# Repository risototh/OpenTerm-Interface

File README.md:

Simple OpenTherm Interface for Arduino or any other MCU.

For Arduino, use the Arduino OpenTherm library at http://ihormelnyk.com/opentherm_library

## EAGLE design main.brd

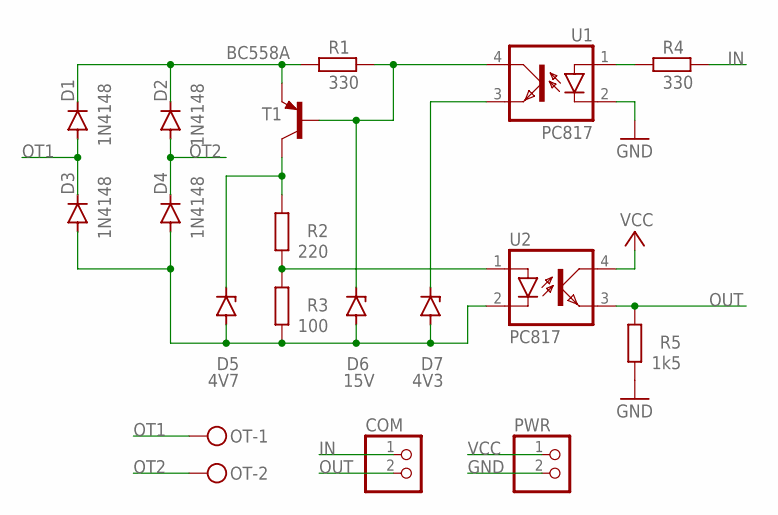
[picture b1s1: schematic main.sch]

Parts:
COM: PINHD-1X2; 1X02
D1, D2, D3, D4: 1N4148; DO35-7
D5: 4V7; ZDIO-7.5
D6: 15V; ZDIO-7.5
D7: 4V3; ZDIO-7.5
OT: MKDSN1,5/2-5,08
PWR: PINHD-1X2; 1X02
R1, R4: 330; 0207/10
R2: 220; 0207/10
R3: 100; 0207/10
R5: 1k5; 0207/10
T1: BC558A; TO92-EBC
U1, U2: PC817; DIL04

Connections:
GND: PWR.2, R5.2, U1.2 (C)
IN: COM.1, R4.2
unnamed: D1.C, D2.C, R1.1, T1.E
unnamed: R2.1, R3.2, U2.1 (A)
unnamed: D5.C, R2.2, T1.C
unnamed: D6.C, R1.2, T1.B, U1.4 (COL)
unnamed: D7.C, U1.3 (EMIT)
unnamed: D3.A, D4.A, D5.A, D6.A, D7.A, R3.1, U2.2 (C)
unnamed: R4.1, U1.1 (A)
OT1: D1.A, D3.C, OT.1
OT2: D2.A, D4.C, OT.2
OUT: COM.2, R5.1, U2.3 (EMIT)
VCC: PWR.1, U2.4 (COL)

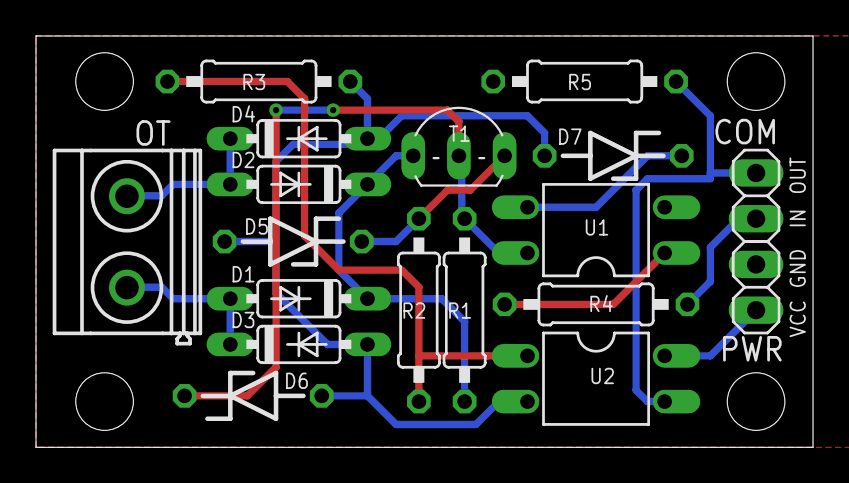
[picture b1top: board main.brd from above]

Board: 2 copper layers, 43.2 x 22.9 mm, 18 parts (0 on the bottom side), 13 nets.

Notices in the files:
main.brd:
(C)2022 creat.io, s.r.o.
